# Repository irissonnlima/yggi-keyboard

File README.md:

# Yggi Keyboard

**Um teclado split ortholinear que vira column stagger com um clique.** Open hardware e open source.

O nome é uma homenagem a Yggdrasil, a árvore que liga os nove mundos da mitologia nórdica. O objetivo de longo prazo é que o Yggi seja o centro que liga os seus computadores e periféricos.

## Conceito de design

> Imagens de conceito para guiar o visual do produto. O projeto técnico (medidas, mecanismo, placas) está em [`hardware/`](hardware/).

**Ortholinear e column stagger.** Em cima, o teclado fechado: um retângulo perfeito, com a baia do e-reader à esquerda. Embaixo, as colunas destravadas e deslizadas no stagger: as colunas externas e a fileira do polegar ficam fixas.

**Colunas que deslizam inteiras.** Cada coluna corre sobre trilhos, e o vão que ela deixa fica aparente e acabado, sem moldura solta.

**E-reader destacável e conectores.** O e-reader tem tela e-ink, três botões, apoio de mesa e USB-C próprio. Ele encaixa na lateral do teclado por uma fileira de contatos pogo, com ímãs acima e abaixo.

## Marca

Três barrinhas iguais em Y, na simetria isométrica (120° entre elas): os dois braços são as metades do teclado e a haste é o tronco que liga tudo, como a Yggdrasil. Os arquivos estão em [`docs/brand/`](docs/brand/): [marca](docs/brand/yggi-marca.svg), [marca branca](docs/brand/yggi-marca-branca.svg), [assinatura](docs/brand/yggi-assinatura.svg) e [ícone do app](docs/brand/yggi-icone.svg).

Na barra de menus do Mac, o ícone é o próprio teclado em miniatura, visto de cima: as colunas sobem conforme o stagger abre (de 0 a 100%), as metades se afastam quando estão separadas, e o ícone fica apagado quando o teclado está desconectado. Clicar nele abre o balão com os widgets.

## Onde está cada coisa

| Pasta | O que tem |
|---|---|
| [`hardware/`](hardware/) | mecanismo de stagger (CAD), placas de circuito, layout das teclas, simulação interativa |
| [`app/`](app/) | app do computador: núcleo em Rust + interface macOS em SwiftUI ([como rodar](app/README.md)) |
| [`docs/`](docs/) | documentação do produto: [funcionalidades](docs/funcionalidades.md), [app](docs/app.md), [arquitetura e testes](docs/arquitetura.md), marca e imagens de conceito |

Ainda virá `firmware/` (ZMK + módulos Yggi).

## Fases

1. **Teclado Bluetooth** com o mecanismo de stagger.
2. **E-reader destacável** que encaixa no teclado.
3. **Hub**: mouse, trackpad e áudio passando pelo Yggi.

**[▶ Simulação interativa](https://htmlpreview.github.io/?https://github.com/irissonnlima/yggi-keyboard/blob/main/hardware/docs/simulacao.html)**

## Licença

A definir. Sugestão: **CERN-OHL-S-2.0** para o hardware e **MIT** para firmware e software.

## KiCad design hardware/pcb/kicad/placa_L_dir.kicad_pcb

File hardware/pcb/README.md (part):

# Placas de circuito do Yggi (rev0)

Cada mão usa **5 placas em cadeia**:

```
placa L  ──►  coluna 1u  ──►  coluna 1u  ──►  coluna 1u  ──►  coluna 2u
(MCU)         (mindinho)      (anelar)        (médio)         (indicador)
```

São **6 projetos** no total, 3 por mão:

| Placa | Esquerda | Direita |
|---|---|---|
| **Placa L** (bloco fixo + barra do polegar, fixa, com o MCU) | esc, Yggi, `` ` ``, tab, caps e shift de 2u; barra com fn, ⌃, ⌥, ⌘, ⌫ e espaço | 8 teclas de 1u (F12, lock, `-`, `=`, `[`, `]`, `'`, `\`) e shift de 2u; barra com espaço, return, ⌘ e 4 setas de meia altura |
| **Coluna 1u** (×3 por mão, **idênticas**) | `coluna_1u` | `coluna_1u_dir` |
| **Coluna 2u** (indicador, fim da cadeia) | `coluna_2u` | `coluna_2u_dir` |

As placas das colunas da direita são as da esquerda com a posição espelhada: a entrada do jumper fica do lado direito. Os switches não são espelhados.

Cada tecla Choc tem um **LED RGB** (SK6812MINI-E). As **setas** da mão direita têm meia altura e o Choc não cabe nelas, então usam uma **chave tátil SMD** (XKB TS-1187A, 5,1 × 5,1 mm) sob um keycap de 0,5u. As setas não têm LED.

As placas saem em duas etapas:
1. O [Ergogen](https://ergogen.xyz) posiciona switches, diodos e pads a partir de [`ergogen/generate.py`](ergogen/generate.py).
2. O [`route.py`](route.py) termina cada placa no KiCad: diodos SOD-123, LEDs RGB, setas táteis, regras da JLCPCB, trilhas pelo [Freerouting](https://github.com/freerouting/freerouting) e DRC.

Os resultados ficam versionados:

| Arquivo | O que é |
|---|---|
| [`kicad/*.kicad_pcb`](kicad/) | as 6 placas roteadas para o KiCad 10, com DRC limpo (0 violações, 0 ligações faltando) |
| [`kicad/teclado_*.kicad_pcb`](kicad/) | **só para ver**: as 10 placas do teclado juntas, na posição do CAD (`teclado_150`: stagger 150%; `teclado_0`: ortho), afastadas para ver onde cada uma acaba. Os jumpers aparecem como linhas de ligação. Gerado por [`assemble.py`](assemble.py) |
| [`kicad/*.kicad_pro`, `*.kicad_dru`](kicad/) | regras de projeto: trilha 0,25, isolamento 0,2, via 0,6/0,3, borda 0,5 mm (0,2 mm só nos pads do LED RGB, que ficam junto do próprio recorte) |
| [`outlines/*.dxf`](outlines/) | contornos de corte, os mesmos usados no CAD |
| [`preview.svg`](preview.svg) | a prévia acima (`python3 hardware/tools/pcb_preview.py`) |

## A ligação em cadeia

Cada placa se liga à vizinha por um **jumper flexível de 13 vias**, que atravessa as paredes das colunas na **faixa livre entre a fileira F e a dos números** (y = 87,25 mm no CAD). É o único corredor sem switches ao longo de toda a coluna.

As colunas vizinhas andam uma em relação à outra quando o stagger muda. Com o perfil padrão em 150%, a diferença é:

| Ligação | Movimento relativo |
|---|---|
| placa L → mindinho | 0 mm |
| mindinho → anelar | 9 mm |
| anelar → médio | 6 mm |
| médio → indicador | 6 mm |

O jumper e os rasgos nas paredes foram dimensionados para **até 15 mm**, então qualquer perfil de placa-came funciona.

- **Protótipo:** 13 fios de silicone 30 AWG, soldados nos pads.
- **Produto:** jumper em placa flexível (FPC) de pé, com 1,6 mm de altura, dobrado em S.

### Barramento rotativo: por que as 3 placas de 1u são iguais

Os dois blocos de pads têm 2 × 7 posições (passo 1,27 mm), na mesma ordem. Dois blocos lado a lado não cabem na coluna de 17,4 mm. Por isso o **J_IN** (entrada) fica 1,6 mm mais para trás e à esquerda, e o **J_OUT** (saída) 1,6 mm mais para a frente e à direita. O jumper liga o J_OUT de uma placa ao J_IN da seguinte, 10,82 mm ao lado. Na mão direita, é o espelho.

| Posição | 1 | 2 | 3 | 4 | 5 | 6 | 7 |
|---|---|---|---|---|---|---|---|
| **J_IN**, linha de cima | R0 | R1 | R2 | R3 | R4 | VLED | GND |
| **J_IN**, linha de baixo | C1 | C2 | C3 | C4 | C5 | — | DIN |
| **J_OUT**, linha de cima | R0 | R1 | R2 | R3 | R4 | VLED | GND |
| **J_OUT**, linha de baixo | C2 | C3 | C4 | C5 | — | — | DOUT |

Cada placa **usa a coluna C1** e repassa as outras deslocadas uma posição. Na placa seguinte, o que era C2 chega como C1, e assim por diante. Por isso a mesma placa serve em qualquer posição da cadeia. A coluna 2u usa C1 e C2 e não tem saída.

Os **dados dos LEDs** entram em DIN, passam pelos LEDs da placa, um depois do outro, e saem em DOUT, na mesma posição do bloco seguinte. VLED e GND passam direto.

### Matriz (uma mão)

**6 linhas × 7 colunas = 13 pinos do MCU**, mais 1 para os LEDs RGB e, na esquerda, 3 para os LEDs da tecla Yggi.

| Linha | Esquerda | Direita |
|---|---|---|
| R0 | fileira F | fileira F |
| R1 | números (inclui a tecla Yggi) | números |
| R2, R3, R4 | letras (tab, caps e shift de 2u em COL0) | letras (shift de 2u em COL0) |
| R5 | barra do polegar (toda na placa L) | barra: espaço COL6, return COL5, ⌘ COL4, ← COL3, ↑ COL2, ↓ COL1, → COL0 |

| Coluna | Onde fica |
|---|---|
| COL0, COL1 | bloco fixo, na placa L |
| COL2 | 1ª placa de 1u (mindinho) |
| COL3 | 2ª placa de 1u (anelar) |
| COL4 | 3ª placa de 1u (médio) |
| COL5, COL6 | placa 2u (indicador) |

Diodos no sentido **COL2ROW**, o padrão do ZMK: coluna → switch → diodo → linha.

### Posição das peças em cada tecla Choc

| Peça | Onde | Face |
|---|---|---|
| LED RGB SK6812MINI-E | 4,7 mm ao sul do centro, na janela do LED do Choc V1, brilhando por um recorte na placa | baixo (montagem invertida) |
| Diodo 1N4148W (SOD-123) | canto noroeste, 3,6 mm à esquerda e 4,5 mm ao norte, na vertical | baixo |

Na barra do polegar os switches ficam girados 180°, e tudo gira junto.

## Decisões e limites da rev0

- **Sem soquete hot-swap Kailh.** O soquete passa ~0,9 mm da borda de uma coluna de 17,4 mm e bateria na parede do trenó. As placas usam os **furos passantes do Choc**: dá para soldar o switch ou usar **soquetes Mill-Max** (tubinhos dentro do furo) e manter a troca de switches.
- **MCU externo na rev0.** Cada placa L tem um **cabeçalho de pads**. Na esquerda são 20: GND, VLED, DIN, R0–R5, COL0–COL6, LED1–3 e GND. Na direita são 17, sem os LEDs da tecla Yggi. Na bancada, ele se liga por fios a uma placa nRF52840 (nice!nano). O VLED vem do VCC chaveado do nice!nano.
- **Na rev1** a eletrônica vai para uma **placa MCU própria na cunha** (módulo nRF52840, carregador, USB-C atrás, chave dos LEDs RGB), ligada à placa L por um flex de 20 vias, mais o conector pogo magnético de 5 pinos, os estabilizadores de 2u e a fixação com M2. Plano completo e posições no CAD: [`rev1.md`](rev1.md).
- **Espessura:** o CAD usa placa de **1,2 mm**. Encomendar com 1,2 mm, ou ajustar `pcb_t` no CAD para 1,6.
- **Trilhas traçadas pelo Freerouting**, em 2 camadas, e conferidas pelo DRC do KiCad. O traçado é automático (funciona, mas não é o mais bonito). O barramento rotativo obriga as trilhas a trocar de face na faixa entre F e números: J_IN e J_OUT têm a mesma ordem, deslocada, e isso não cabe numa face só.
- **LEDs RGB (SK6812MINI-E):** um por tecla Choc, 38 na mão esquerda e 35 na direita. Cuidados:
  - cada LED gasta **~1 mA mesmo apagado** (~75 mA por mão). Por isso a energia deles precisa ser cortada quando estiverem desligados: o VCC chaveado do nice!nano na rev0 e um MOSFET na rev1;
  - em branco total, cada LED puxa até 60 mA, o que dá mais de 2 A por mão. O **brilho precisa ser limitado no firmware**, e as trilhas de 0,25 mm e os fios de 30 AWG do jumper não aguentam o brilho máximo;
  - o SK6812 foi feito para 3,7–5,5 V. No VCC de 3,3 V do nice!nano ele funciona, mas o azul e o branco ficam mais fracos;
  - a posição da janela do LED (4,7 mm ao sul) segue os projetos de referência com Choc V1. **Conferir com um switch na mão** antes de fabricar;
  - os pads do LED ficam a 0,25 mm do canto do recorte, como no footprint oficial do KiCad. O mínimo de borda da placa fica em 0,2 mm, e a regra em `*.kicad_dru` volta a exigir 0,5 mm de todo o resto;
  - um capacitor de 4,7 µF por placa, entre VLED e GND.
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
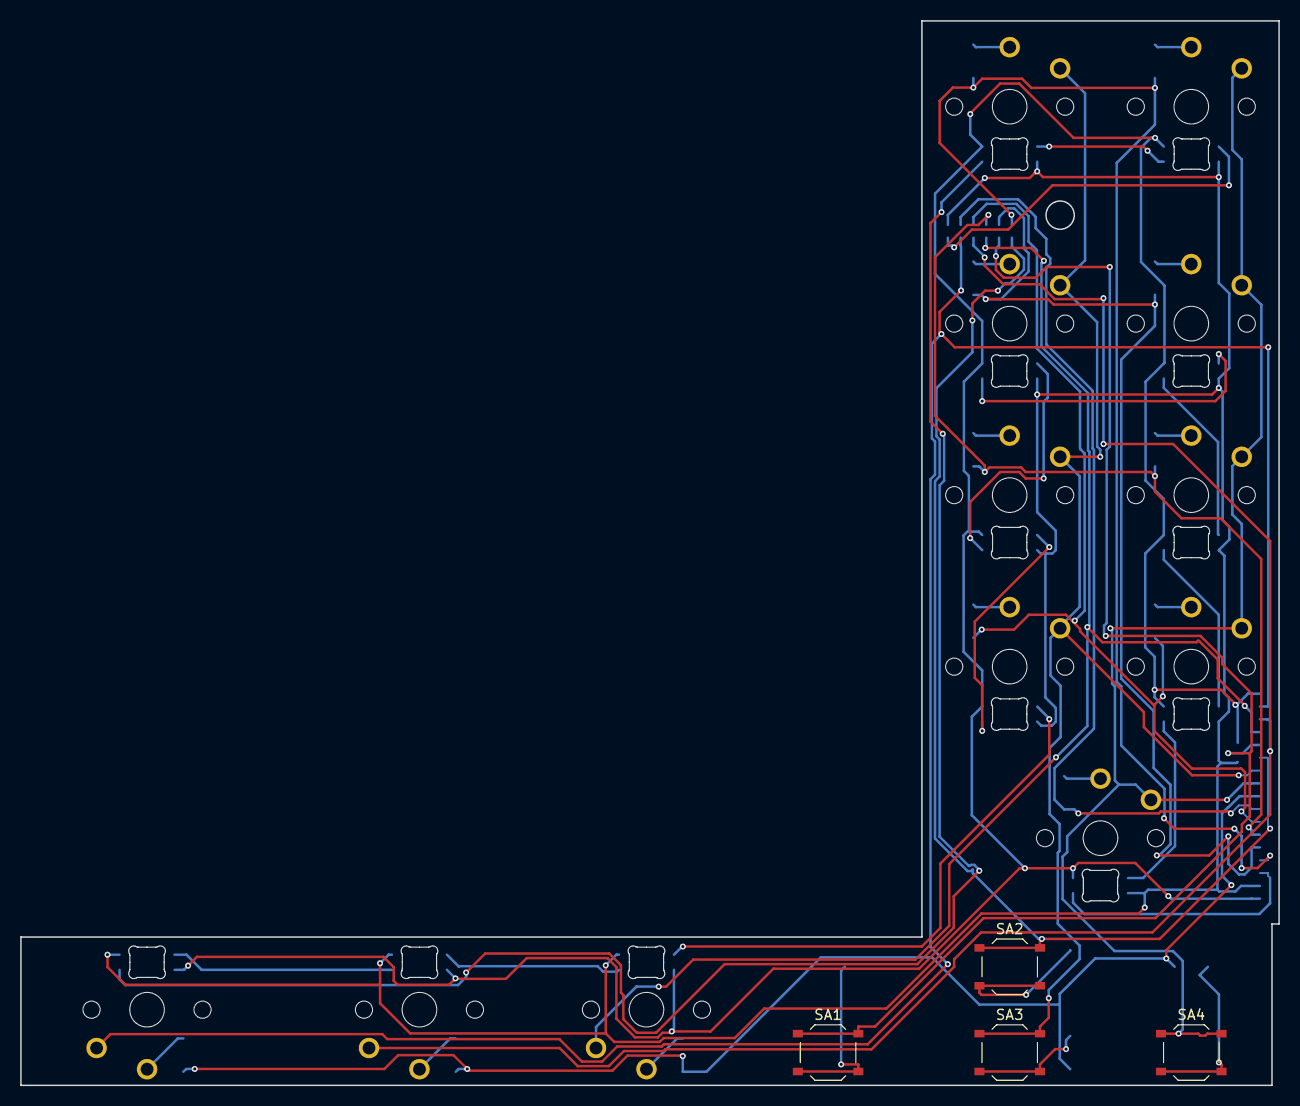
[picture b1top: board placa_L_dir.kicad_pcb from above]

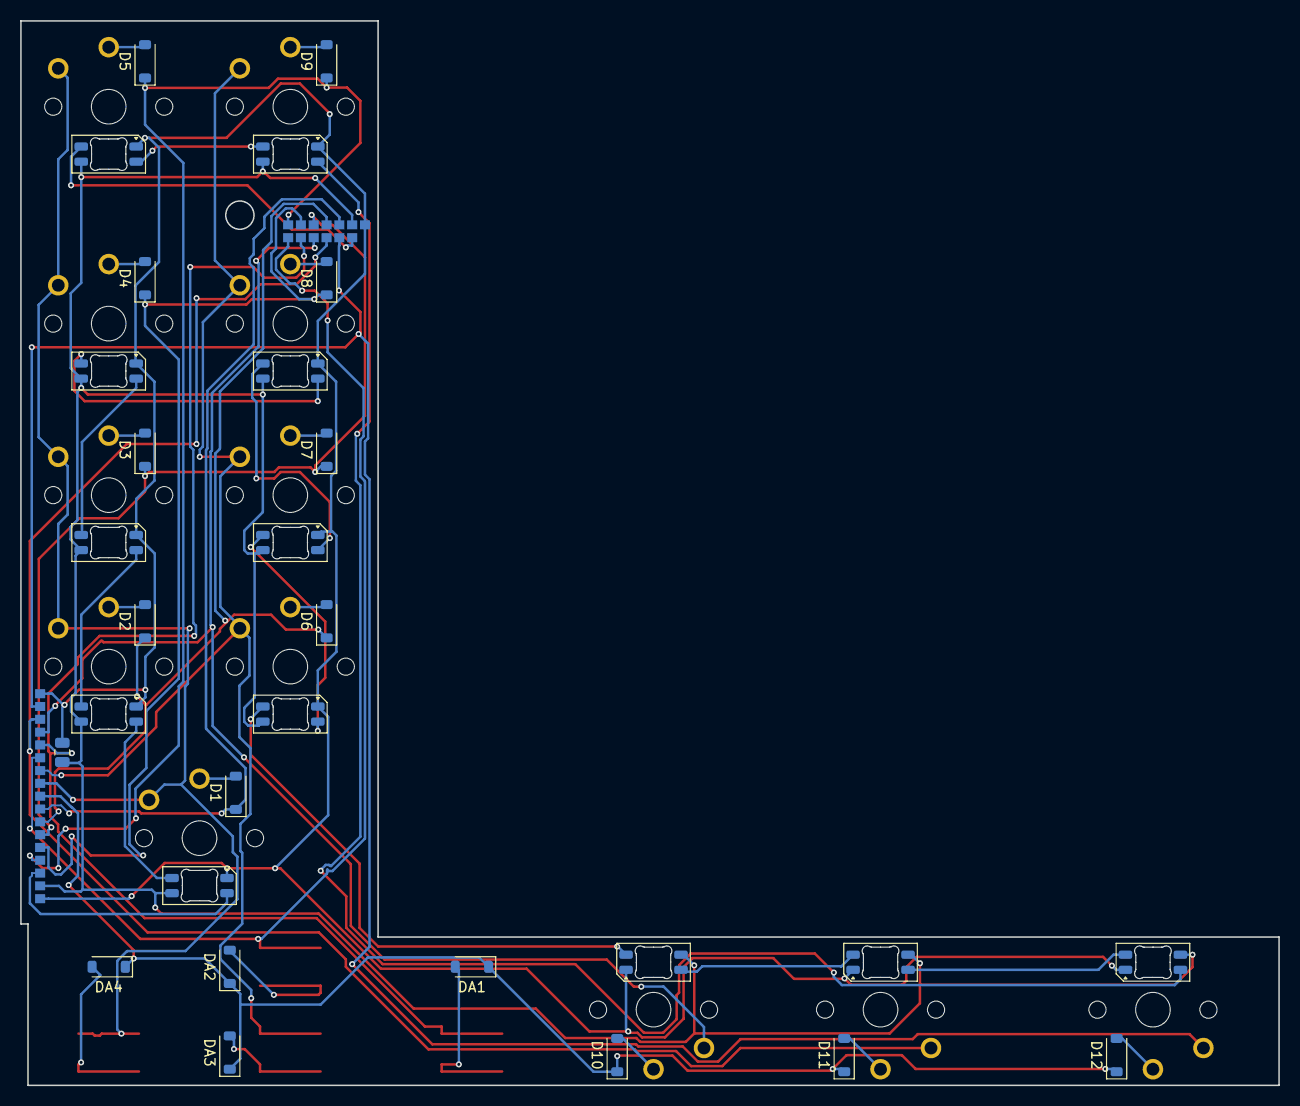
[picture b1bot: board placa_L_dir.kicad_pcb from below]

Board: 2 copper layers, 124.7 x 105.5 mm, 75 parts (29 on the bottom side), 44 nets.

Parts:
C1: 4.7uF; C_0805_2012Metric
D1, D2, D3, D4, D5, D6, D7, D8, D9, D10, D11, D12: 1N4148W; D_SOD-123
DA1, DA2, DA3, DA4: 1N4148W; D_SOD-123
L1, L2, L3, L4, L5, L6, L7, L8, L9, L10, L11, L12: SK6812MINI-E; LED_SK6812MINI-E_3.2x2.8mm_P1.5mm_ReverseMount
PAD1, PAD2, PAD3, PAD4, PAD5, PAD6, PAD7, PAD8, PAD9, PAD10, PAD11, PAD12, PAD13, PAD14, PAD15, PAD16, PAD17, PAD18, PAD19, PAD20, PAD21, PAD22, PAD23, PAD24, PAD25, PAD26, PAD27, PAD28, PAD29, PAD30: SMDPad
S1, S2, S3, S4, S5, S6, S7, S8, S9, S10, S11, S12: PG1350
SA1, SA2, SA3, SA4: TS-1187A; SW_Push_1P1T_XKB_TS-1187A

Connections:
COL0: PAD23.1, S1.1, S2.1, S3.1, S4.1, S5.1, SA4.1
COL1: PAD24.1, S6.1, S7.1, S8.1, S9.1, SA3.1
COL2: PAD8.1, PAD25.1, SA2.1
COL3: PAD9.1, PAD26.1, SA1.1
COL4: PAD10.1, PAD27.1, S10.1
COL5: PAD11.1, PAD28.1, S11.1
COL6: PAD12.1, PAD29.1, S12.1
DIN: L1.2, PAD16.1
DOUT: L12.4, PAD13.1
GND: C1.2, L1.1, L2.1, L3.1, L4.1, L5.1, L6.1, L7.1, L8.1, L9.1, L10.1, L11.1, L12.1, PAD7.1, PAD14.1, PAD30.1
R0: D5.1, D9.1, PAD1.1, PAD17.1
R1: D4.1, D8.1, PAD2.1, PAD18.1
R2: D3.1, D7.1, PAD3.1, PAD19.1
R3: D2.1, D6.1, PAD4.1, PAD20.1
R4: D1.1, PAD5.1, PAD21.1
R5: D10.1, D11.1, D12.1, DA1.1, DA2.1, DA3.1, DA4.1, PAD22.1
VLED: C1.1, L1.3, L2.3, L3.3, L4.3, L5.3, L6.3, L7.3, L8.3, L9.3, L10.3, L11.3, L12.3, PAD6.1, PAD15.1
arw_down: DA3.2, SA3.2
arw_left: DA1.2, SA1.2
arw_right: DA4.2, SA4.2
arw_up: DA2.2, SA2.2
c0_r0: D5.2, S5.2
c0_r1: D4.2, S4.2
c0_r2: D3.2, S3.2
c0_r3: D2.2, S2.2
c0_r4: D1.2, S1.2
c1_r0: D9.2, S9.2
c1_r1: D8.2, S8.2
c1_r2: D7.2, S7.2
c1_r3: D6.2, S6.2
cmd_r5: D10.2, S10.2
ret_r5: D11.2, S11.2
rgb1: L1.4, L2.2
rgb2: L2.4, L3.2
rgb3: L3.4, L4.2
rgb4: L4.4, L5.2
rgb5: L5.4, L6.2
rgb6: L6.4, L7.2
rgb7: L7.4, L8.2
rgb8: L8.4, L9.2
rgb9: L9.4, L10.2
rgb10: L10.4, L11.2
rgb11: L11.4, L12.2
spc_r5: D12.2, S12.2

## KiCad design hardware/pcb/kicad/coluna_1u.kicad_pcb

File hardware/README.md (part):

# Yggi Keyboard · hardware

**Um teclado split ortholinear que vira column stagger com um clique.** Open hardware e open source.

Em ortholinear, as duas metades formam um retângulo perfeito, como um teclado comum. Aperte o botão ao lado dos LEDs e uma mola faz as colunas deslizarem inteiras até o stagger escolhido (50, 100 ou 150%). Para voltar, empurre as colunas até ouvir o clique.

O nome é uma homenagem a Yggdrasil, a árvore que liga os nove mundos da mitologia nórdica. O objetivo de longo prazo é que o Yggi seja o centro que liga os seus computadores e periféricos.

**[▶ Abrir a simulação interativa](https://htmlpreview.github.io/?https://github.com/irissonnlima/yggi-keyboard/blob/main/hardware/docs/simulacao.html)** ([arquivo](docs/simulacao.html)): vista de cima com antes e depois, corte lateral, **raio-x dos circuitos** (as 5 placas em cadeia, jumpers, MCU, bateria, USB-C, ímãs e pogo), diagrama das ligações e o ciclo da mola em corte.

---

## Estado atual

| | |
|---|---|
| **Fase** | 1 · teclado Bluetooth com mecanismo de stagger |
| **CAD** | [`stagger-mechanism/yggi_v3.scad`](stagger-mechanism/yggi_v3.scad) (OpenSCAD, paramétrico) |
| **Layout** | [`layout/yggi-v9-B-ortho.json`](layout/yggi-v9-B-ortho.json) (Keyboard Layout Editor) |
| **Verificado** | todas as peças compilam; nenhuma colisão entre peças em 0, 50, 100 e 150% |
| **Ainda não testado** | nada foi impresso ou montado |

| Ortholinear (0%) | Column stagger (150%) |
|---|---|
|  |  |

**Vista lateral** (inclinação de 5° dada pela cunha da bateria):

**Metade esquerda explodida** (cunha com bateria, bandeja, placa-came, chassi, colunas com as suas placas, bloco fixo, placa L e barra do polegar; na rev1, a placa MCU fica na cunha, ao lado da bateria: veja [`pcb/rev1.md`](pcb/rev1.md)):

**Placas de circuito** ([detalhes](pcb/README.md)): as 6 placas das duas mãos (placa L com o bloco fixo e a barra do polegar, coluna 1u e coluna 2u), geradas com Ergogen e roteadas no KiCad, com LED RGB por tecla:

---

## Layout

Split 7 + 7 colunas com layout Mac, 79 teclas, mais uma baia para um e-reader destacável.

- **2 colunas externas fixas de cada lado:** esc, a **tecla Yggi** (troca de computador) com **3 LEDs** que indicam o aparelho, `` ` ``, e tab, caps e shift de 2u.
- **Colunas móveis:** mindinho, anelar, médio e indicador. Cada uma sobe o quanto o dedo precisa: médio +15 mm, anelar e indicador +9 mm, mindinho 0.
- **Barra do polegar fixa:** fn ⌃ ⌥ ⌘ ⌫ ␣ | ␣ ↩ ⌘ e setas de 0,5u, no estilo Magic Keyboard.
- **Baia de 4u × 6,5u** para um e-reader do tamanho do XTeink X4 (69 × 114 mm).

**Tecla Yggi:** toque vai para o próximo computador pareado. Segurar + 1…5 vai direto para um computador. Segurar 3 s entra em pareamento. A troca só acontece ao soltar a tecla, então um toque acidental não muda nada.

---

## Como o mecanismo funciona

Cada metade, de baixo para cima:

1. **Cunha** (impressa): cria a inclinação de 5° e guarda a **bateria**, o tambor da **mola** e o curso da **trava**.
2. **Bandeja**: bolsão da placa-came, canal da fita da mola e dos fios, lingueta da trava e furos do batente.
3. **Placa-came** (chapa de 1,2 mm): tem 8 rasgos inclinados, 2 por coluna móvel. Ao deslizar 24 mm em X, empurra cada coluna em Y na proporção do rasgo. A posição dos pinos foi escolhida por busca para os rasgos nunca se cruzarem (folga mínima de 9 mm).
4. **Chassi imutável** (chapa de 1,6 mm): rasgos-guia em Y. Fica sempre escondido embaixo das colunas.
5. **Gavetas**: cada coluna móvel é um trenó impresso com **a sua própria placa de circuito** em cima (switches Choc montados direto na placa). As placas se ligam **em cadeia**, de uma coluna para a vizinha, por um jumper flexível que atravessa as paredes na faixa entre a fileira F e a dos números. Dois pinos-parafuso por gaveta fazem o papel de guia, came e trava contra levantar. A **saia** da frente sai de baixo da barra do polegar e tampa o vão quando a coluna sobe.
6. **Bloco fixo** e **barra do polegar**: não se movem.

**Mola e trava:**
- Uma **mola de força constante** (fita de aço, tipo trena) puxa a placa-came para o stagger o tempo todo.
- Em ortho, uma **lingueta** com dente entra num furo da placa e segura tudo.
- O **botão** ao lado dos LEDs empurra o dente para baixo, e a mola leva as colunas até o **pino de batente** (50, 100 ou 150%, trocável por baixo).
- Para voltar, é só empurrar as colunas. Os rasgos são inclinados o bastante (~32°) para o movimento voltar pela came, e o dente estala de volta no furo.

**Módulos:** as faces de encaixe são retas, com ímãs de 4 × 2 mm e um **conector pogo magnético de 5 pinos** (VBUS, GND, 2 de dados e detecção) na face da bandeja. As bordas externas são arredondadas. Com as metades juntas, um único USB-C carrega tudo. Separadas, cada metade funciona sozinha por Bluetooth.

---

## Eletrônica

| | |
|---|---|
| **Placas por metade** | **5, em cadeia**: placa L (bloco fixo + barra do polegar) → coluna 1u → coluna 1u → coluna 1u → coluna 2u. As 3 de 1u são **idênticas**, graças a um barramento rotativo. |
| **Microcontrolador** | um **nRF52840** (módulo Raytac MDBT50Q) por metade, numa **placa MCU própria na cunha**, sob o bloco fixo, com a antena na borda externa. Junto ficam o carregador, a chave dos LEDs e o **USB-C, na face de trás da cunha**. Um flex de 20 vias liga a placa MCU à placa L. Na rev0 das placas, o MCU é externo (nice!nano ligado por fios). Plano: [`pcb/rev1.md`](pcb/rev1.md). |
| **Por que nRF52840** | é o chip mais bem suportado pelo ZMK. Tem 21 GPIO, o suficiente para a matriz 6 × 7 mais os 3 LEDs. |
| **Firmware** | [ZMK](https://zmk.dev) (Zephyr, MIT): Bluetooth, split sem fio, 5 perfis de computador, bateria. Funções do Yggi (tecla de troca, LEDs, conversa com o e-reader) entram como **módulos ZMK** próprios. |
| **Bateria** | LiPo de 4 mm na cunha, ~1800 mAh por metade (76 × 46 mm). A cunha comporta células maiores se a inclinação aumentar. |
| **Ligação das colunas** | **jumper de 13 vias** (5 linhas, 5 colunas, VLED, GND e dados dos LEDs) entre placas vizinhas. Colunas vizinhas andam no máximo 9 mm uma em relação à outra no perfil padrão; o projeto aceita até 15 mm. Protótipo: fios de silicone. Produto: jumper flexível (FPC). |
| **Switches** | Choc V1 com **furos passantes** (soldados ou em soquetes Mill-Max). O soquete hot-swap Kailh não cabe numa coluna de 17,4 mm. As 4 setas de meia altura (mão direita) usam chave tátil SMD (TS-1187A). |
| **Iluminação** | **LED RGB por tecla** (SK6812MINI-E, montado por baixo, brilhando pela janela do Choc): 38 na mão esquerda e 35 na direita, em cadeia de uma placa para a seguinte. Mais os 3 LEDs de aparelho da tecla Yggi. |

O **e-reader** (fase 2) tem cérebro próprio. A base sugerida é o firmware open source [CrossPoint](https://github.com/crosspoint-reader/crosspoint-reader) (ESP32). Encaixado, ele mostra o estado do teclado. Solto, é um leitor.

---

## Estrutura da pasta `hardware/`

```
docs/
  simulacao.html          simulação interativa: vista de cima, corte, raio-x e mola
  media/                  GIF e imagens do README
pcb/
  ergogen/generate.py     gera as placas (Ergogen)
  route.py                termina as placas no KiCad (LEDs, diodos, trilhas pelo Freerouting, DRC)
  assemble.py             junta as 10 placas num arquivo só, para ver o teclado inteiro
  kicad/                  as 6 placas (placa L, coluna 1u, coluna 2u; esquerda e _dir) e teclado_*.kicad_pcb
  outlines/               contornos de corte (.dxf)
stagger-mechanism/
  yggi_v3.scad            CAD atual (mecanismo fino, inclinado, com mola)
  yggi_v2.scad            versão anterior (histórico)
  yggi_stagger.scad       primeiro protótipo, 5 colunas (histórico)
  renders/                imagens geradas pelo OpenSCAD
layout/
  yggi-v9-B-*.json        layout atual para o Keyboard Layout Editor
tools/
  make_gif.py             junta os PNGs do OpenSCAD num GIF (sem dependências)
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
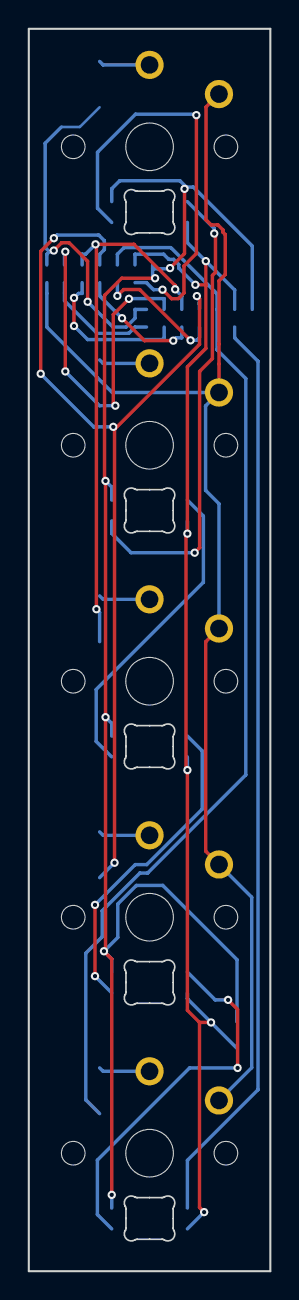
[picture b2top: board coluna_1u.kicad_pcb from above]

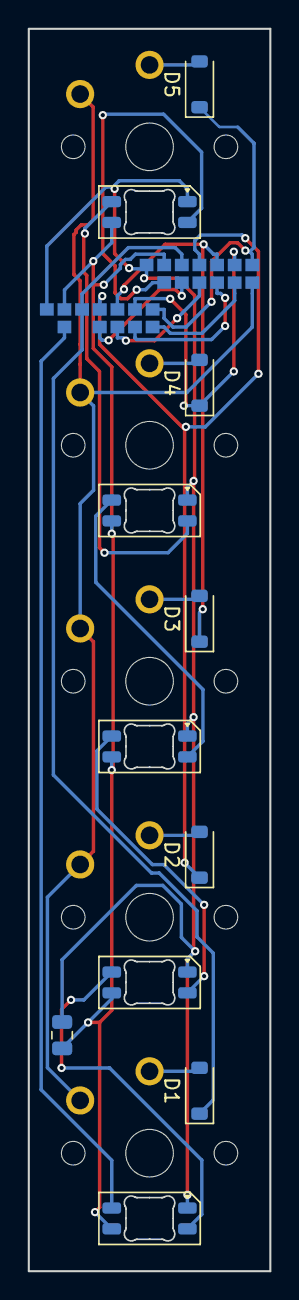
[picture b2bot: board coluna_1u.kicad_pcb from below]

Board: 2 copper layers, 17.4 x 89.5 mm, 41 parts (11 on the bottom side), 23 nets.

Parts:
C1: 4.7uF; C_0805_2012Metric
D1, D2, D3, D4, D5: 1N4148W; D_SOD-123
L1, L2, L3, L4, L5: SK6812MINI-E; LED_SK6812MINI-E_3.2x2.8mm_P1.5mm_ReverseMount
PAD1, PAD2, PAD3, PAD4, PAD5, PAD6, PAD7, PAD8, PAD9, PAD10, PAD11, PAD12, PAD13, PAD14, PAD15, PAD16, PAD17, PAD18, PAD19, PAD20, PAD21, PAD22, PAD23, PAD24, PAD25: SMDPad
S1, S2, S3, S4, S5: PG1350

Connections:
C1: PAD8.1, S1.1, S2.1, S3.1, S4.1, S5.1
C2: PAD9.1, PAD21.1
C3: PAD10.1, PAD22.1
C4: PAD11.1, PAD23.1
C5: PAD12.1, PAD24.1
DIN: L1.2, PAD13.1
DOUT: L5.4, PAD25.1
GND: C1.2, L1.1, L2.1, L3.1, L4.1, L5.1, PAD7.1, PAD20.1
R0: D5.1, PAD1.1, PAD14.1
R1: D4.1, PAD2.1, PAD15.1
R2: D3.1, PAD3.1, PAD16.1
R3: D2.1, PAD4.1, PAD17.1
R4: D1.1, PAD5.1, PAD18.1
VLED: C1.1, L1.3, L2.3, L3.3, L4.3, L5.3, PAD6.1, PAD19.1
c1_r0: D5.2, S5.2
c1_r1: D4.2, S4.2
c1_r2: D3.2, S3.2
c1_r3: D2.2, S2.2
c1_r4: D1.2, S1.2
rgb1: L1.4, L2.2
rgb2: L2.4, L3.2
rgb3: L3.4, L4.2
rgb4: L4.4, L5.2

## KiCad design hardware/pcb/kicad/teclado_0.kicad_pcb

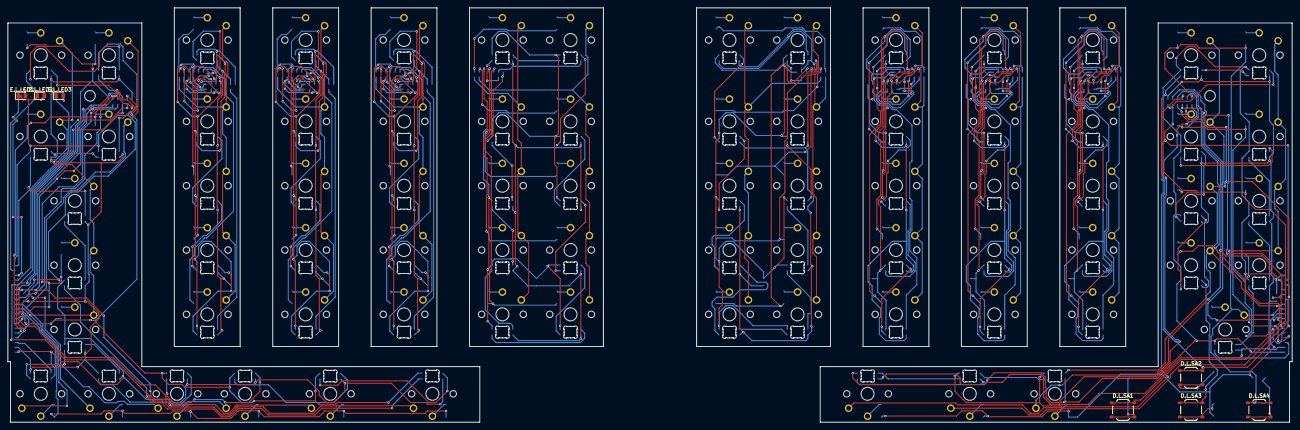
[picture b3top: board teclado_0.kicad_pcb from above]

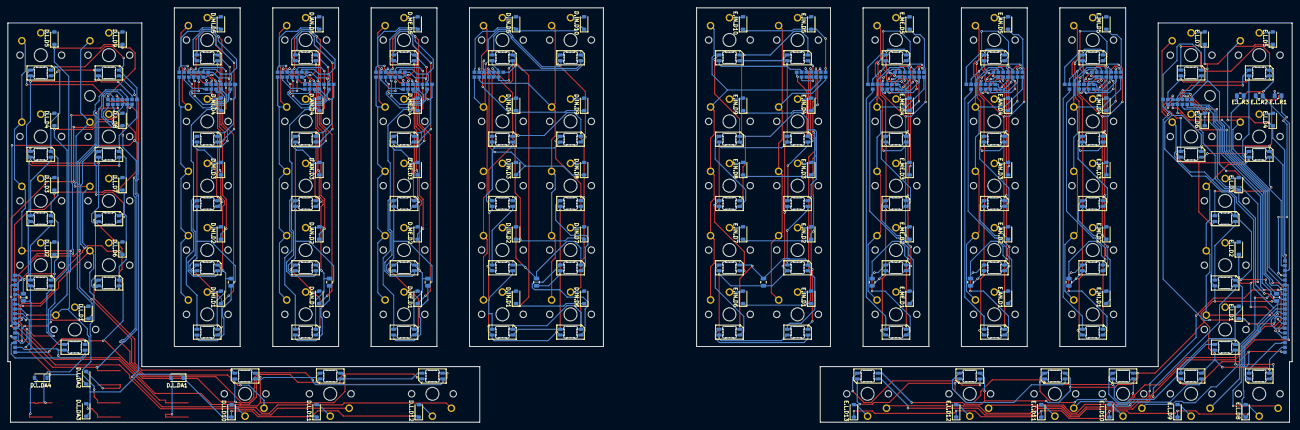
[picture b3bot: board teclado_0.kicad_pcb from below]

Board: 2 copper layers, 339.4 x 109.5 mm, 488 parts (167 on the bottom side), 196 nets.

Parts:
D.AN.C1, D.IN.C1, D.L.C1, D.ME.C1, D.MI.C1: 4.7uF; C_0805_2012Metric
D.AN.D1, D.AN.D2, D.AN.D3, D.AN.D4, D.AN.D5, D.IN.D1, D.IN.D2, D.IN.D3, D.IN.D4, D.IN.D5, D.IN.D6, D.IN.D7, D.IN.D8, D.IN.D9, D.IN.D10, D.L.D1, D.L.D2, D.L.D3, D.L.D4, D.L.D5, D.L.D6, D.L.D7, D.L.D8, D.L.D9, D.L.D10, D.L.D11, D.L.D12, D.L.DA1, D.L.DA2, D.L.DA3, D.L.DA4, D.ME.D1, D.ME.D2, D.ME.D3, D.ME.D4, D.ME.D5, D.MI.D1, D.MI.D2, D.MI.D3, D.MI.D4, D.MI.D5: 1N4148W; D_SOD-123
D.AN.L1, D.AN.L2, D.AN.L3, D.AN.L4, D.AN.L5, D.IN.L1, D.IN.L2, D.IN.L3, D.IN.L4, D.IN.L5, D.IN.L6, D.IN.L7, D.IN.L8, D.IN.L9, D.IN.L10, D.L.L1, D.L.L2, D.L.L3, D.L.L4, D.L.L5, D.L.L6, D.L.L7, D.L.L8, D.L.L9, D.L.L10, D.L.L11, D.L.L12, D.ME.L1, D.ME.L2, D.ME.L3, D.ME.L4, D.ME.L5, D.MI.L1, D.MI.L2, D.MI.L3, D.MI.L4, D.MI.L5: SK6812MINI-E; LED_SK6812MINI-E_3.2x2.8mm_P1.5mm_ReverseMount
D.AN.PAD1, D.AN.PAD2, D.AN.PAD3, D.AN.PAD4, D.AN.PAD5, D.AN.PAD6, D.AN.PAD7, D.AN.PAD8, D.AN.PAD9, D.AN.PAD10, D.AN.PAD11, D.AN.PAD12, D.AN.PAD13, D.AN.PAD14, D.AN.PAD15, D.AN.PAD16, D.AN.PAD17, D.AN.PAD18, D.AN.PAD19, D.AN.PAD20, D.AN.PAD21, D.AN.PAD22, D.AN.PAD23, D.AN.PAD24, D.AN.PAD25, D.IN.PAD1, D.IN.PAD2, D.IN.PAD3, D.IN.PAD4, D.IN.PAD5, D.IN.PAD6, D.IN.PAD7, D.IN.PAD8, D.IN.PAD9, D.IN.PAD10, D.IN.PAD11, D.IN.PAD12, D.IN.PAD13, D.L.PAD1, D.L.PAD2, D.L.PAD3, D.L.PAD4, D.L.PAD5, D.L.PAD6, D.L.PAD7, D.L.PAD8, D.L.PAD9, D.L.PAD10, D.L.PAD11, D.L.PAD12, D.L.PAD13, D.L.PAD14, D.L.PAD15, D.L.PAD16, D.L.PAD17, D.L.PAD18, D.L.PAD19, D.L.PAD20, D.L.PAD21, D.L.PAD22, D.L.PAD23, D.L.PAD24, D.L.PAD25, D.L.PAD26, D.L.PAD27, D.L.PAD28, D.L.PAD29, D.L.PAD30, D.ME.PAD1, D.ME.PAD2, D.ME.PAD3, D.ME.PAD4, D.ME.PAD5, D.ME.PAD6, D.ME.PAD7, D.ME.PAD8, D.ME.PAD9, D.ME.PAD10, D.ME.PAD11, D.ME.PAD12, D.ME.PAD13, D.ME.PAD14, D.ME.PAD15, D.ME.PAD16, D.ME.PAD17, D.ME.PAD18, D.ME.PAD19, D.ME.PAD20, D.ME.PAD21, D.ME.PAD22, D.ME.PAD23, D.ME.PAD24, D.ME.PAD25, D.MI.PAD1, D.MI.PAD2, D.MI.PAD3, D.MI.PAD4, D.MI.PAD5, D.MI.PAD6, D.MI.PAD7, D.MI.PAD8, D.MI.PAD9, D.MI.PAD10, D.MI.PAD11, D.MI.PAD12, D.MI.PAD13, D.MI.PAD14, D.MI.PAD15, D.MI.PAD16, D.MI.PAD17, D.MI.PAD18, D.MI.PAD19, D.MI.PAD20, D.MI.PAD21, D.MI.PAD22, D.MI.PAD23, D.MI.PAD24, D.MI.PAD25: SMDPad
D.AN.S1, D.AN.S2, D.AN.S3, D.AN.S4, D.AN.S5, D.IN.S1, D.IN.S2, D.IN.S3, D.IN.S4, D.IN.S5, D.IN.S6, D.IN.S7, D.IN.S8, D.IN.S9, D.IN.S10, D.L.S1, D.L.S2, D.L.S3, D.L.S4, D.L.S5, D.L.S6, D.L.S7, D.L.S8, D.L.S9, D.L.S10, D.L.S11, D.L.S12, D.ME.S1, D.ME.S2, D.ME.S3, D.ME.S4, D.ME.S5, D.MI.S1, D.MI.S2, D.MI.S3, D.MI.S4, D.MI.S5: PG1350
D.L.SA1, D.L.SA2, D.L.SA3, D.L.SA4: TS-1187A; SW_Push_1P1T_XKB_TS-1187A
E.AN.C1, E.IN.C1, E.L.C1, E.ME.C1, E.MI.C1: 4.7uF; C_0805_2012Metric
E.AN.D1, E.AN.D2, E.AN.D3, E.AN.D4, E.AN.D5, E.IN.D1, E.IN.D2, E.IN.D3, E.IN.D4, E.IN.D5, E.IN.D6, E.IN.D7, E.IN.D8, E.IN.D9, E.IN.D10, E.L.D1, E.L.D2, E.L.D3, E.L.D4, E.L.D5, E.L.D6, E.L.D7, E.L.D8, E.L.D9, E.L.D10, E.L.D11, E.L.D12, E.L.D13, E.ME.D1, E.ME.D2, E.ME.D3, E.ME.D4, E.ME.D5, E.MI.D1, E.MI.D2, E.MI.D3, E.MI.D4, E.MI.D5: 1N4148W; D_SOD-123
E.AN.L1, E.AN.L2, E.AN.L3, E.AN.L4, E.AN.L5, E.IN.L1, E.IN.L2, E.IN.L3, E.IN.L4, E.IN.L5, E.IN.L6, E.IN.L7, E.IN.L8, E.IN.L9, E.IN.L10, E.L.L1, E.L.L2, E.L.L3, E.L.L4, E.L.L5, E.L.L6, E.L.L7, E.L.L8, E.L.L9, E.L.L10, E.L.L11, E.L.L12, E.L.L13, E.ME.L1, E.ME.L2, E.ME.L3, E.ME.L4, E.ME.L5, E.MI.L1, E.MI.L2, E.MI.L3, E.MI.L4, E.MI.L5: SK6812MINI-E; LED_SK6812MINI-E_3.2x2.8mm_P1.5mm_ReverseMount
E.AN.PAD1, E.AN.PAD2, E.AN.PAD3, E.AN.PAD4, E.AN.PAD5, E.AN.PAD6, E.AN.PAD7, E.AN.PAD8, E.AN.PAD9, E.AN.PAD10, E.AN.PAD11, E.AN.PAD12, E.AN.PAD13, E.AN.PAD14, E.AN.PAD15, E.AN.PAD16, E.AN.PAD17, E.AN.PAD18, E.AN.PAD19, E.AN.PAD20, E.AN.PAD21, E.AN.PAD22, E.AN.PAD23, E.AN.PAD24, E.AN.PAD25, E.IN.PAD1, E.IN.PAD2, E.IN.PAD3, E.IN.PAD4, E.IN.PAD5, E.IN.PAD6, E.IN.PAD7, E.IN.PAD8, E.IN.PAD9, E.IN.PAD10, E.IN.PAD11, E.IN.PAD12, E.IN.PAD13, E.L.PAD1, E.L.PAD2, E.L.PAD3, E.L.PAD4, E.L.PAD5, E.L.PAD6, E.L.PAD7, E.L.PAD8, E.L.PAD9, E.L.PAD10, E.L.PAD11, E.L.PAD12, E.L.PAD13, E.L.PAD14, E.L.PAD15, E.L.PAD16, E.L.PAD17, E.L.PAD18, E.L.PAD19, E.L.PAD20, E.L.PAD21, E.L.PAD22, E.L.PAD23, E.L.PAD24, E.L.PAD25, E.L.PAD26, E.L.PAD27, E.L.PAD28, E.L.PAD29, E.L.PAD30, E.L.PAD31, E.L.PAD32, E.L.PAD33, E.ME.PAD1, E.ME.PAD2, E.ME.PAD3, E.ME.PAD4, E.ME.PAD5, E.ME.PAD6, E.ME.PAD7, E.ME.PAD8, E.ME.PAD9, E.ME.PAD10, E.ME.PAD11, E.ME.PAD12, E.ME.PAD13, E.ME.PAD14, E.ME.PAD15, E.ME.PAD16, E.ME.PAD17, E.ME.PAD18, E.ME.PAD19, E.ME.PAD20, E.ME.PAD21, E.ME.PAD22, E.ME.PAD23, E.ME.PAD24, E.ME.PAD25, E.MI.PAD1, E.MI.PAD2, E.MI.PAD3, E.MI.PAD4, E.MI.PAD5, E.MI.PAD6, E.MI.PAD7, E.MI.PAD8, E.MI.PAD9, E.MI.PAD10, E.MI.PAD11, E.MI.PAD12, E.MI.PAD13, E.MI.PAD14, E.MI.PAD15, E.MI.PAD16, E.MI.PAD17, E.MI.PAD18, E.MI.PAD19, E.MI.PAD20, E.MI.PAD21, E.MI.PAD22, E.MI.PAD23, E.MI.PAD24, E.MI.PAD25: SMDPad
E.AN.S1, E.AN.S2, E.AN.S3, E.AN.S4, E.AN.S5, E.IN.S1, E.IN.S2, E.IN.S3, E.IN.S4, E.IN.S5, E.IN.S6, E.IN.S7, E.IN.S8, E.IN.S9, E.IN.S10, E.L.S1, E.L.S2, E.L.S3, E.L.S4, E.L.S5, E.L.S6, E.L.S7, E.L.S8, E.L.S9, E.L.S10, E.L.S11, E.L.S12, E.L.S13, E.ME.S1, E.ME.S2, E.ME.S3, E.ME.S4, E.ME.S5, E.MI.S1, E.MI.S2, E.MI.S3, E.MI.S4, E.MI.S5: PG1350
E.L.LED1, E.L.LED2, E.L.LED3: LED 0805; LED_0805_2012Metric
E.L.R1, E.L.R2, E.L.R3: 1k; R_0805_2012Metric

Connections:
D.AN.c1_r0: D.AN.D5.2, D.AN.S5.2
D.AN.c1_r1: D.AN.D4.2, D.AN.S4.2
D.AN.c1_r2: D.AN.D3.2, D.AN.S3.2
D.AN.c1_r3: D.AN.D2.2, D.AN.S2.2
D.AN.c1_r4: D.AN.D1.2, D.AN.S1.2
D.AN.livre.C5: D.AN.PAD12.1, D.AN.PAD24.1
D.AN.rgb1: D.AN.L1.4, D.AN.L2.2
D.AN.rgb2: D.AN.L2.4, D.AN.L3.2
D.AN.rgb3: D.AN.L3.4, D.AN.L4.2
D.AN.rgb4: D.AN.L4.4, D.AN.L5.2
D.COL0: D.L.PAD23.1, D.L.S1.1, D.L.S2.1, D.L.S3.1, D.L.S4.1, D.L.S5.1, D.L.SA4.1
D.COL1: D.L.PAD24.1, D.L.S6.1, D.L.S7.1, D.L.S8.1, D.L.S9.1, D.L.SA3.1
D.COL2: D.L.PAD8.1, D.L.PAD25.1, D.L.SA2.1, D.MI.PAD8.1, D.MI.S1.1, D.MI.S2.1, D.MI.S3.1, D.MI.S4.1, D.MI.S5.1
D.COL3: D.AN.PAD8.1, D.AN.S1.1, D.AN.S2.1, D.AN.S3.1, D.AN.S4.1, D.AN.S5.1, D.L.PAD9.1, D.L.PAD26.1, D.L.SA1.1, D.MI.PAD9.1, D.MI.PAD21.1
D.COL4: D.AN.PAD9.1, D.AN.PAD21.1, D.L.PAD10.1, D.L.PAD27.1, D.L.S10.1, D.ME.PAD8.1, D.ME.S1.1, D.ME.S2.1, D.ME.S3.1, D.ME.S4.1, D.ME.S5.1, D.MI.PAD10.1, D.MI.PAD22.1
D.COL5: D.AN.PAD10.1, D.AN.PAD22.1, D.IN.PAD8.1, D.IN.S1.1, D.IN.S2.1, D.IN.S3.1, D.IN.S4.1, D.IN.S5.1, D.L.PAD11.1, D.L.PAD28.1, D.L.S11.1, D.ME.PAD9.1, D.ME.PAD21.1, D.MI.PAD11.1, D.MI.PAD23.1
D.COL6: D.AN.PAD11.1, D.AN.PAD23.1, D.IN.PAD9.1, D.IN.S6.1, D.IN.S7.1, D.IN.S8.1, D.IN.S9.1, D.IN.S10.1, D.L.PAD12.1, D.L.PAD29.1, D.L.S12.1, D.ME.PAD10.1, D.ME.PAD22.1, D.MI.PAD12.1, D.MI.PAD24.1
D.DAT0: D.L.L1.2, D.L.PAD16.1
D.DAT1: D.L.L12.4, D.L.PAD13.1, D.MI.L1.2, D.MI.PAD13.1
D.DAT2: D.AN.L1.2, D.AN.PAD13.1, D.MI.L5.4, D.MI.PAD25.1
D.DAT3: D.AN.L5.4, D.AN.PAD25.1, D.ME.L1.2, D.ME.PAD13.1
D.DAT4: D.IN.L1.2, D.IN.PAD13.1, D.ME.L5.4, D.ME.PAD25.1
D.GND: D.AN.C1.2, D.AN.L1.1, D.AN.L2.1, D.AN.L3.1, D.AN.L4.1, D.AN.L5.1, D.AN.PAD7.1, D.AN.PAD20.1, D.IN.C1.2, D.IN.L1.1, D.IN.L2.1, D.IN.L3.1, D.IN.L4.1, D.IN.L5.1, D.IN.L6.1, D.IN.L7.1, D.IN.L8.1, D.IN.L9.1, D.IN.L10.1, D.IN.PAD7.1, D.L.C1.2, D.L.L1.1, D.L.L2.1, D.L.L3.1, D.L.L4.1, D.L.L5.1, D.L.L6.1, D.L.L7.1, D.L.L8.1, D.L.L9.1, D.L.L10.1, D.L.L11.1, D.L.L12.1, D.L.PAD7.1, D.L.PAD14.1, D.L.PAD30.1, D.ME.C1.2, D.ME.L1.1, D.ME.L2.1, D.ME.L3.1, D.ME.L4.1, D.ME.L5.1, D.ME.PAD7.1, D.ME.PAD20.1, D.MI.C1.2, D.MI.L1.1, D.MI.L2.1, D.MI.L3.1, D.MI.L4.1, D.MI.L5.1, D.MI.PAD7.1, D.MI.PAD20.1
D.IN.c1_r0: D.IN.D5.2, D.IN.S5.2
D.IN.c1_r1: D.IN.D4.2, D.IN.S4.2
D.IN.c1_r2: D.IN.D3.2, D.IN.S3.2
D.IN.c1_r3: D.IN.D2.2, D.IN.S2.2
D.IN.c1_r4: D.IN.D1.2, D.IN.S1.2
D.IN.c2_r0: D.IN.D10.2, D.IN.S10.2
D.IN.c2_r1: D.IN.D9.2, D.IN.S9.2
D.IN.c2_r2: D.IN.D8.2, D.IN.S8.2
D.IN.c2_r3: D.IN.D7.2, D.IN.S7.2
D.IN.c2_r4: D.IN.D6.2, D.IN.S6.2
D.IN.rgb1: D.IN.L1.4, D.IN.L2.2
D.IN.rgb2: D.IN.L2.4, D.IN.L3.2
D.IN.rgb3: D.IN.L3.4, D.IN.L4.2
D.IN.rgb4: D.IN.L4.4, D.IN.L5.2
D.IN.rgb5: D.IN.L5.4, D.IN.L6.2
D.IN.rgb6: D.IN.L6.4, D.IN.L7.2
D.IN.rgb7: D.IN.L7.4, D.IN.L8.2
D.IN.rgb8: D.IN.L8.4, D.IN.L9.2
D.IN.rgb9: D.IN.L9.4, D.IN.L10.2
D.L.arw_down: D.L.DA3.2, D.L.SA3.2
D.L.arw_left: D.L.DA1.2, D.L.SA1.2
D.L.arw_right: D.L.DA4.2, D.L.SA4.2
D.L.arw_up: D.L.DA2.2, D.L.SA2.2
D.L.c0_r0: D.L.D5.2, D.L.S5.2
D.L.c0_r1: D.L.D4.2, D.L.S4.2
D.L.c0_r2: D.L.D3.2, D.L.S3.2
D.L.c0_r3: D.L.D2.2, D.L.S2.2
D.L.c0_r4: D.L.D1.2, D.L.S1.2
D.L.c1_r0: D.L.D9.2, D.L.S9.2
D.L.c1_r1: D.L.D8.2, D.L.S8.2
D.L.c1_r2: D.L.D7.2, D.L.S7.2
D.L.c1_r3: D.L.D6.2, D.L.S6.2
D.L.cmd_r5: D.L.D10.2, D.L.S10.2
D.L.ret_r5: D.L.D11.2, D.L.S11.2
D.L.rgb1: D.L.L1.4, D.L.L2.2
D.L.rgb2: D.L.L2.4, D.L.L3.2
D.L.rgb3: D.L.L3.4, D.L.L4.2
D.L.rgb4: D.L.L4.4, D.L.L5.2
D.L.rgb5: D.L.L5.4, D.L.L6.2
D.L.rgb6: D.L.L6.4, D.L.L7.2
D.L.rgb7: D.L.L7.4, D.L.L8.2
D.L.rgb8: D.L.L8.4, D.L.L9.2
D.L.rgb9: D.L.L9.4, D.L.L10.2
D.L.rgb10: D.L.L10.4, D.L.L11.2
D.L.rgb11: D.L.L11.4, D.L.L12.2
D.L.spc_r5: D.L.D12.2, D.L.S12.2
D.ME.c1_r0: D.ME.D5.2, D.ME.S5.2
D.ME.c1_r1: D.ME.D4.2, D.ME.S4.2
D.ME.c1_r2: D.ME.D3.2, D.ME.S3.2
D.ME.c1_r3: D.ME.D2.2, D.ME.S2.2
D.ME.c1_r4: D.ME.D1.2, D.ME.S1.2
D.ME.livre.C4: D.ME.PAD11.1, D.ME.PAD23.1
D.ME.livre.C5: D.ME.PAD12.1, D.ME.PAD24.1
D.ME.rgb1: D.ME.L1.4, D.ME.L2.2
D.ME.rgb2: D.ME.L2.4, D.ME.L3.2
D.ME.rgb3: D.ME.L3.4, D.ME.L4.2
D.ME.rgb4: D.ME.L4.4, D.ME.L5.2
D.MI.c1_r0: D.MI.D5.2, D.MI.S5.2
D.MI.c1_r1: D.MI.D4.2, D.MI.S4.2
D.MI.c1_r2: D.MI.D3.2, D.MI.S3.2
D.MI.c1_r3: D.MI.D2.2, D.MI.S2.2
D.MI.c1_r4: D.MI.D1.2, D.MI.S1.2
D.MI.rgb1: D.MI.L1.4, D.MI.L2.2
D.MI.rgb2: D.MI.L2.4, D.MI.L3.2
D.MI.rgb3: D.MI.L3.4, D.MI.L4.2
D.MI.rgb4: D.MI.L4.4, D.MI.L5.2
D.R0: D.AN.D5.1, D.AN.PAD1.1, D.AN.PAD14.1, D.IN.D5.1, D.IN.D10.1, D.IN.PAD1.1, D.L.D5.1, D.L.D9.1, D.L.PAD1.1, D.L.PAD17.1, D.ME.D5.1, D.ME.PAD1.1, D.ME.PAD14.1, D.MI.D5.1, D.MI.PAD1.1, D.MI.PAD14.1
D.R1: D.AN.D4.1, D.AN.PAD2.1, D.AN.PAD15.1, D.IN.D4.1, D.IN.D9.1, D.IN.PAD2.1, D.L.D4.1, D.L.D8.1, D.L.PAD2.1, D.L.PAD18.1, D.ME.D4.1, D.ME.PAD2.1, D.ME.PAD15.1, D.MI.D4.1, D.MI.PAD2.1, D.MI.PAD15.1
D.R2: D.AN.D3.1, D.AN.PAD3.1, D.AN.PAD16.1, D.IN.D3.1, D.IN.D8.1, D.IN.PAD3.1, D.L.D3.1, D.L.D7.1, D.L.PAD3.1, D.L.PAD19.1, D.ME.D3.1, D.ME.PAD3.1, D.ME.PAD16.1, D.MI.D3.1, D.MI.PAD3.1, D.MI.PAD16.1
D.R3: D.AN.D2.1, D.AN.PAD4.1, D.AN.PAD17.1, D.IN.D2.1, D.IN.D7.1, D.IN.PAD4.1, D.L.D2.1, D.L.D6.1, D.L.PAD4.1, D.L.PAD20.1, D.ME.D2.1, D.ME.PAD4.1, D.ME.PAD17.1, D.MI.D2.1, D.MI.PAD4.1, D.MI.PAD17.1
D.R4: D.AN.D1.1, D.AN.PAD5.1, D.AN.PAD18.1, D.IN.D1.1, D.IN.D6.1, D.IN.PAD5.1, D.L.D1.1, D.L.PAD5.1, D.L.PAD21.1, D.ME.D1.1, D.ME.PAD5.1, D.ME.PAD18.1, D.MI.D1.1, D.MI.PAD5.1, D.MI.PAD18.1
D.R5: D.L.D10.1, D.L.D11.1, D.L.D12.1, D.L.DA1.1, D.L.DA2.1, D.L.DA3.1, D.L.DA4.1, D.L.PAD22.1
D.VLED: D.AN.C1.1, D.AN.L1.3, D.AN.L2.3, D.AN.L3.3, D.AN.L4.3, D.AN.L5.3, D.AN.PAD6.1, D.AN.PAD19.1, D.IN.C1.1, D.IN.L1.3, D.IN.L2.3, D.IN.L3.3, D.IN.L4.3, D.IN.L5.3, D.IN.L6.3, D.IN.L7.3, D.IN.L8.3, D.IN.L9.3, D.IN.L10.3, D.IN.PAD6.1, D.L.C1.1, D.L.L1.3, D.L.L2.3, D.L.L3.3, D.L.L4.3, D.L.L5.3, D.L.L6.3, D.L.L7.3, D.L.L8.3, D.L.L9.3, D.L.L10.3, D.L.L11.3, D.L.L12.3, D.L.PAD6.1, D.L.PAD15.1, D.ME.C1.1, D.ME.L1.3, D.ME.L2.3, D.ME.L3.3, D.ME.L4.3, D.ME.L5.3, D.ME.PAD6.1, D.ME.PAD19.1, D.MI.C1.1, D.MI.L1.3, D.MI.L2.3, D.MI.L3.3, D.MI.L4.3, D.MI.L5.3, D.MI.PAD6.1, D.MI.PAD19.1
E.AN.c1_r0: E.AN.D5.2, E.AN.S5.2
E.AN.c1_r1: E.AN.D4.2, E.AN.S4.2
E.AN.c1_r2: E.AN.D3.2, E.AN.S3.2
E.AN.c1_r3: E.AN.D2.2, E.AN.S2.2
E.AN.c1_r4: E.AN.D1.2, E.AN.S1.2
E.AN.livre.C5: E.AN.PAD12.1, E.AN.PAD24.1
E.AN.rgb1: E.AN.L1.4, E.AN.L2.2
E.AN.rgb2: E.AN.L2.4, E.AN.L3.2
E.AN.rgb3: E.AN.L3.4, E.AN.L4.2
E.AN.rgb4: E.AN.L4.4, E.AN.L5.2
E.COL0: E.L.PAD23.1, E.L.S1.1, E.L.S2.1, E.L.S3.1, E.L.S4.1, E.L.S5.1, E.L.S8.1
E.COL1: E.L.PAD24.1, E.L.S6.1, E.L.S7.1, E.L.S9.1
E.COL2: E.L.PAD8.1, E.L.PAD25.1, E.L.S10.1, E.MI.PAD8.1, E.MI.S1.1, E.MI.S2.1, E.MI.S3.1, E.MI.S4.1, E.MI.S5.1
E.COL3: E.AN.PAD8.1, E.AN.S1.1, E.AN.S2.1, E.AN.S3.1, E.AN.S4.1, E.AN.S5.1, E.L.PAD9.1, E.L.PAD26.1, E.L.S11.1, E.MI.PAD9.1, E.MI.PAD21.1
E.COL4: E.AN.PAD9.1, E.AN.PAD21.1, E.L.PAD10.1, E.L.PAD27.1, E.L.S12.1, E.ME.PAD8.1, E.ME.S1.1, E.ME.S2.1, E.ME.S3.1, E.ME.S4.1, E.ME.S5.1, E.MI.PAD10.1, E.MI.PAD22.1
E.COL5: E.AN.PAD10.1, E.AN.PAD22.1, E.IN.PAD8.1, E.IN.S1.1, E.IN.S2.1, E.IN.S3.1, E.IN.S4.1, E.IN.S5.1, E.L.PAD11.1, E.L.PAD28.1, E.L.S13.1, E.ME.PAD9.1, E.ME.PAD21.1, E.MI.PAD11.1, E.MI.PAD23.1
E.COL6: E.AN.PAD11.1, E.AN.PAD23.1, E.IN.PAD9.1, E.IN.S6.1, E.IN.S7.1, E.IN.S8.1, E.IN.S9.1, E.IN.S10.1, E.L.PAD12.1, E.L.PAD29.1, E.ME.PAD10.1, E.ME.PAD22.1, E.MI.PAD12.1, E.MI.PAD24.1
E.DAT0: E.L.L1.2, E.L.PAD16.1
E.DAT1: E.L.L13.4, E.L.PAD13.1, E.MI.L1.2, E.MI.PAD13.1
E.DAT2: E.AN.L1.2, E.AN.PAD13.1, E.MI.L5.4, E.MI.PAD25.1
E.DAT3: E.AN.L5.4, E.AN.PAD25.1, E.ME.L1.2, E.ME.PAD13.1
E.DAT4: E.IN.L1.2, E.IN.PAD13.1, E.ME.L5.4, E.ME.PAD25.1
E.GND: E.AN.C1.2, E.AN.L1.1, E.AN.L2.1, E.AN.L3.1, E.AN.L4.1, E.AN.L5.1, E.AN.PAD7.1, E.AN.PAD20.1, E.IN.C1.2, E.IN.L1.1, E.IN.L2.1, E.IN.L3.1, E.IN.L4.1, E.IN.L5.1, E.IN.L6.1, E.IN.L7.1, E.IN.L8.1, E.IN.L9.1, E.IN.L10.1, E.IN.PAD7.1, E.L.C1.2, E.L.L1.1, E.L.L2.1, E.L.L3.1, E.L.L4.1, E.L.L5.1, E.L.L6.1, E.L.L7.1, E.L.L8.1, E.L.L9.1, E.L.L10.1, E.L.L11.1, E.L.L12.1, E.L.L13.1, E.L.LED1.1, E.L.LED2.1, E.L.LED3.1, E.L.PAD7.1, E.L.PAD14.1, E.L.PAD33.1, E.ME.C1.2, E.ME.L1.1, E.ME.L2.1, E.ME.L3.1, E.ME.L4.1, E.ME.L5.1, E.ME.PAD7.1, E.ME.PAD20.1, E.MI.C1.2, E.MI.L1.1, E.MI.L2.1, E.MI.L3.1, E.MI.L4.1, E.MI.L5.1, E.MI.PAD7.1, E.MI.PAD20.1
E.IN.c1_r0: E.IN.D5.2, E.IN.S5.2
E.IN.c1_r1: E.IN.D4.2, E.IN.S4.2
E.IN.c1_r2: E.IN.D3.2, E.IN.S3.2
E.IN.c1_r3: E.IN.D2.2, E.IN.S2.2
E.IN.c1_r4: E.IN.D1.2, E.IN.S1.2
E.IN.c2_r0: E.IN.D10.2, E.IN.S10.2
E.IN.c2_r1: E.IN.D9.2, E.IN.S9.2
E.IN.c2_r2: E.IN.D8.2, E.IN.S8.2
E.IN.c2_r3: E.IN.D7.2, E.IN.S7.2
E.IN.c2_r4: E.IN.D6.2, E.IN.S6.2
E.IN.rgb1: E.IN.L1.4, E.IN.L2.2
E.IN.rgb2: E.IN.L2.4, E.IN.L3.2
E.IN.rgb3: E.IN.L3.4, E.IN.L4.2
E.IN.rgb4: E.IN.L4.4, E.IN.L5.2
E.IN.rgb5: E.IN.L5.4, E.IN.L6.2
E.IN.rgb6: E.IN.L6.4, E.IN.L7.2
E.IN.rgb7: E.IN.L7.4, E.IN.L8.2
E.IN.rgb8: E.IN.L8.4, E.IN.L9.2
E.IN.rgb9: E.IN.L9.4, E.IN.L10.2
E.L.c0_r0: E.L.D5.2, E.L.S5.2
E.L.c0_r1: E.L.D4.2, E.L.S4.2
E.L.c0_r2: E.L.D3.2, E.L.S3.2
E.L.c0_r3: E.L.D2.2, E.L.S2.2
E.L.c0_r4: E.L.D1.2, E.L.S1.2
E.L.c1_r0: E.L.D7.2, E.L.S7.2
E.L.c1_r1: E.L.D6.2, E.L.S6.2
E.L.cmd_r5: E.L.D11.2, E.L.S11.2
E.L.ctl_r5: E.L.D9.2, E.L.S9.2
E.L.del_r5: E.L.D12.2, E.L.S12.2
E.L.fn_r5: E.L.D8.2, E.L.S8.2
E.L.led1_a: E.L.LED1.2, E.L.R1.2
E.L.led2_a: E.L.LED2.2, E.L.R2.2
E.L.led3_a: E.L.LED3.2, E.L.R3.2
E.L.opt_r5: E.L.D10.2, E.L.S10.2
E.L.rgb1: E.L.L1.4, E.L.L2.2
E.L.rgb2: E.L.L2.4, E.L.L3.2
E.L.rgb3: E.L.L3.4, E.L.L4.2
E.L.rgb4: E.L.L4.4, E.L.L5.2
E.L.rgb5: E.L.L5.4, E.L.L6.2
E.L.rgb6: E.L.L6.4, E.L.L7.2
E.L.rgb7: E.L.L7.4, E.L.L8.2
E.L.rgb8: E.L.L8.4, E.L.L9.2
E.L.rgb9: E.L.L9.4, E.L.L10.2
E.L.rgb10: E.L.L10.4, E.L.L11.2
E.L.rgb11: E.L.L11.4, E.L.L12.2
E.L.rgb12: E.L.L12.4, E.L.L13.2
E.L.spc_r5: E.L.D13.2, E.L.S13.2
E.LED1: E.L.PAD30.1, E.L.R1.1
E.LED2: E.L.PAD31.1, E.L.R2.1
E.LED3: E.L.PAD32.1, E.L.R3.1
E.ME.c1_r0: E.ME.D5.2, E.ME.S5.2
E.ME.c1_r1: E.ME.D4.2, E.ME.S4.2
E.ME.c1_r2: E.ME.D3.2, E.ME.S3.2
E.ME.c1_r3: E.ME.D2.2, E.ME.S2.2
E.ME.c1_r4: E.ME.D1.2, E.ME.S1.2
E.ME.livre.C4: E.ME.PAD11.1, E.ME.PAD23.1
E.ME.livre.C5: E.ME.PAD12.1, E.ME.PAD24.1
E.ME.rgb1: E.ME.L1.4, E.ME.L2.2
E.ME.rgb2: E.ME.L2.4, E.ME.L3.2
E.ME.rgb3: E.ME.L3.4, E.ME.L4.2
E.ME.rgb4: E.ME.L4.4, E.ME.L5.2
E.MI.c1_r0: E.MI.D5.2, E.MI.S5.2
E.MI.c1_r1: E.MI.D4.2, E.MI.S4.2
E.MI.c1_r2: E.MI.D3.2, E.MI.S3.2
E.MI.c1_r3: E.MI.D2.2, E.MI.S2.2
E.MI.c1_r4: E.MI.D1.2, E.MI.S1.2
E.MI.rgb1: E.MI.L1.4, E.MI.L2.2
E.MI.rgb2: E.MI.L2.4, E.MI.L3.2
E.MI.rgb3: E.MI.L3.4, E.MI.L4.2
E.MI.rgb4: E.MI.L4.4, E.MI.L5.2
E.R0: E.AN.D5.1, E.AN.PAD1.1, E.AN.PAD14.1, E.IN.D5.1, E.IN.D10.1, E.IN.PAD1.1, E.L.D5.1, E.L.D7.1, E.L.PAD1.1, E.L.PAD17.1, E.ME.D5.1, E.ME.PAD1.1, E.ME.PAD14.1, E.MI.D5.1, E.MI.PAD1.1, E.MI.PAD14.1
E.R1: E.AN.D4.1, E.AN.PAD2.1, E.AN.PAD15.1, E.IN.D4.1, E.IN.D9.1, E.IN.PAD2.1, E.L.D4.1, E.L.D6.1, E.L.PAD2.1, E.L.PAD18.1, E.ME.D4.1, E.ME.PAD2.1, E.ME.PAD15.1, E.MI.D4.1, E.MI.PAD2.1, E.MI.PAD15.1
E.R2: E.AN.D3.1, E.AN.PAD3.1, E.AN.PAD16.1, E.IN.D3.1, E.IN.D8.1, E.IN.PAD3.1, E.L.D3.1, E.L.PAD3.1, E.L.PAD19.1, E.ME.D3.1, E.ME.PAD3.1, E.ME.PAD16.1, E.MI.D3.1, E.MI.PAD3.1, E.MI.PAD16.1
E.R3: E.AN.D2.1, E.AN.PAD4.1, E.AN.PAD17.1, E.IN.D2.1, E.IN.D7.1, E.IN.PAD4.1, E.L.D2.1, E.L.PAD4.1, E.L.PAD20.1, E.ME.D2.1, E.ME.PAD4.1, E.ME.PAD17.1, E.MI.D2.1, E.MI.PAD4.1, E.MI.PAD17.1
E.R4: E.AN.D1.1, E.AN.PAD5.1, E.AN.PAD18.1, E.IN.D1.1, E.IN.D6.1, E.IN.PAD5.1, E.L.D1.1, E.L.PAD5.1, E.L.PAD21.1, E.ME.D1.1, E.ME.PAD5.1, E.ME.PAD18.1, E.MI.D1.1, E.MI.PAD5.1, E.MI.PAD18.1
E.R5: E.L.D8.1, E.L.D9.1, E.L.D10.1, E.L.D11.1, E.L.D12.1, E.L.D13.1, E.L.PAD22.1
E.VLED: E.AN.C1.1, E.AN.L1.3, E.AN.L2.3, E.AN.L3.3, E.AN.L4.3, E.AN.L5.3, E.AN.PAD6.1, E.AN.PAD19.1, E.IN.C1.1, E.IN.L1.3, E.IN.L2.3, E.IN.L3.3, E.IN.L4.3, E.IN.L5.3, E.IN.L6.3, E.IN.L7.3, E.IN.L8.3, E.IN.L9.3, E.IN.L10.3, E.IN.PAD6.1, E.L.C1.1, E.L.L1.3, E.L.L2.3, E.L.L3.3, E.L.L4.3, E.L.L5.3, E.L.L6.3, E.L.L7.3, E.L.L8.3, E.L.L9.3, E.L.L10.3, E.L.L11.3, E.L.L12.3, E.L.L13.3, E.L.PAD6.1, E.L.PAD15.1, E.ME.C1.1, E.ME.L1.3, E.ME.L2.3, E.ME.L3.3, E.ME.L4.3, E.ME.L5.3, E.ME.PAD6.1, E.ME.PAD19.1, E.MI.C1.1, E.MI.L1.3, E.MI.L2.3, E.MI.L3.3, E.MI.L4.3, E.MI.L5.3, E.MI.PAD6.1, E.MI.PAD19.1

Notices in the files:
hardware/README.md:
A definir. Sugestão: **CERN-OHL-S-2.0** para o hardware e **MIT** para o firmware, a mesma do ZMK.
